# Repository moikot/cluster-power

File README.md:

# Cluster power

Two PCBs designed to provide Raspberry Pis or similar single-board computers with 5V and up to 3A current. 

[Power board](#power-board)  
[Power bridge](#power-bridge)  

## Power board

A circuit diagram and a PCB design for a modular power supply. It's based on a DC-DC step-down voltage buck converter module and can supply a Raspberry Pi or a similar single-board computer with 5V and up to 3A current. 

You can connect several power boards in a chain using [AVX bipolar card edge connector Series 9159](https://no.mouser.com/ProductDetail/581-00915900201106) and provide power to a cluster of Raspberry Pis. 

### Technical characteristics

* Input voltage: 7V-28V DC
* Output voltage: 5V DC
* Output current: 3A. max (2A for a long time)

### Components

* 3 x 7V-28V to 5V DC-DC step-down voltage buck converter [module](https://www.aliexpress.com/item/32728471522.html).
* Fixed Terminal Block [PTSM 0,5/ 2-2,5-H](https://no.mouser.com/ProductDetail/651-1770885).
* 2 postions x 2 rows [board to board connector](https://no.mouser.com/ProductDetail/200-SSW10201GD).
* 100µF 50V Aluminum [electrolytic capacitor](https://www.digikey.no/product-detail/en/panasonic-electronic-components/ECA-1HM101/P5182-ND/245041).

## Power Bridge

A circuit diagram and a PCB design for a small board for connecting  [Power board](#power-board)  to a Raspberry Pi or a similar single-board computer and providing power through its GPIO.

### Components
* 2 postions x 2 rows right angle [header](https://no.mouser.com/ProductDetail/200-TSW10208LDRA).
* 5 postions x 2 rows [board to board connector](https://no.mouser.com/ProductDetail/200-SSW10501GD).

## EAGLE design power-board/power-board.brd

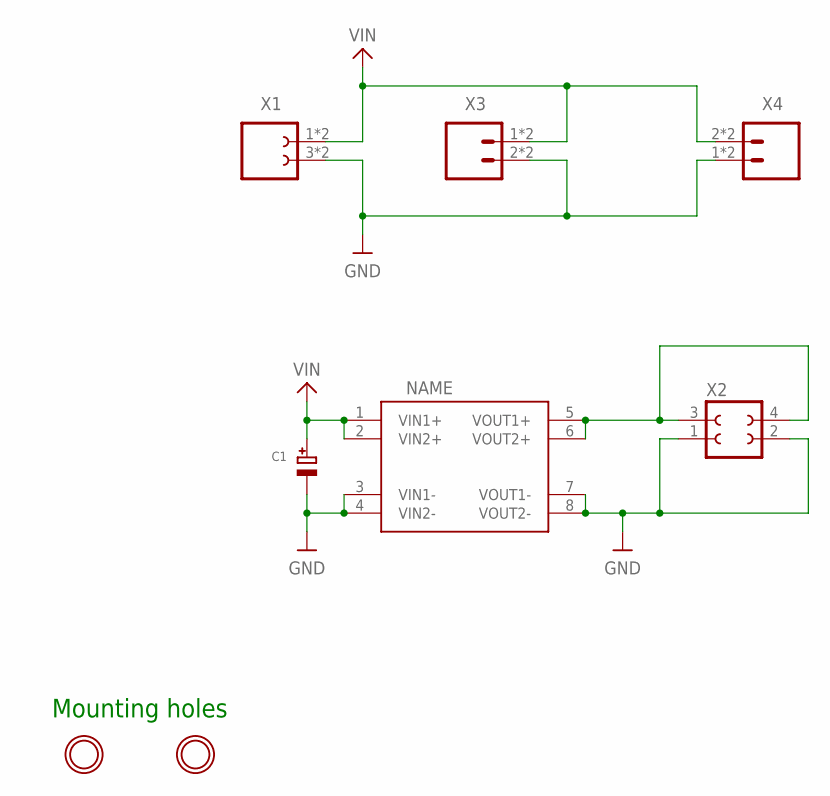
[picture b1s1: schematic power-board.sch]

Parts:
C1: CAP_ELECTROLYTIC; CAPPRD350W60D800H800B
PS1: K8801MODULE; K8801
U$2, U$3: MOUNTINGHOLE2.7_THICK; MOUNTINGHOLE_2.7_PLATED_THICK
X1: CON-FE02-1; PTSM0,5/2-2,5-HTHRR24
X2: CON-FE02-2HDRVR4W64P254_2X2; HDRVR4W64P254_2X2
X3, X4: CON-MA02-1; AVX-BTB-009159002001106

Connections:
GND: C1.2 (-), PS1.3 (VIN1-), PS1.4 (VIN2-), PS1.7 (VOUT1-), PS1.8 (VOUT2-), X1.3, X1.4 (3), X2.1, X2.2, X3.2 (4), X3.4, X4.1 (2), X4.3 (2)
unnamed: PS1.5 (VOUT1+), PS1.6 (VOUT2+), X2.3, X2.4
VIN: C1.1 (+), PS1.1 (VIN1+), PS1.2 (VIN2+), X1.1, X1.2 (1), X3.1 (2), X3.3 (2), X4.2 (4), X4.4

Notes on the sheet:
Mounting holes

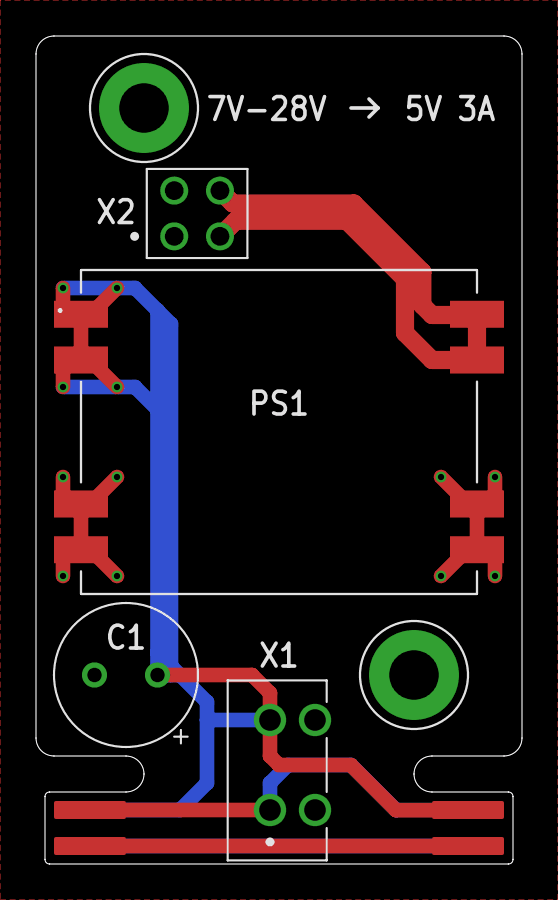
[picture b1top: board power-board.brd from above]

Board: 2 copper layers, 27.0 x 46.0 mm, 8 parts (0 on the bottom side), 3 nets.

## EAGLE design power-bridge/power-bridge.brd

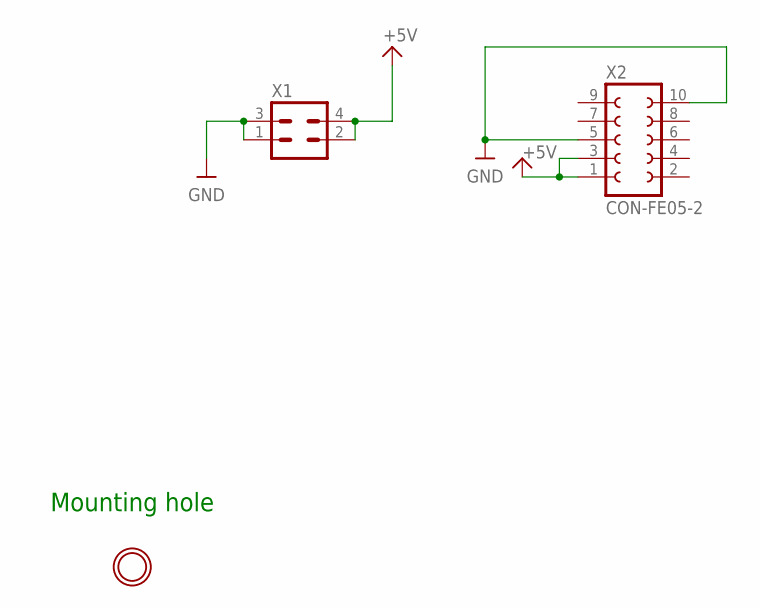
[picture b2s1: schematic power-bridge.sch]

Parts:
U$1: MOUNTINGHOLE2.7_THICK; MOUNTINGHOLE_2.7_PLATED_THICK
X1: CON-MA02-2; HDRRA4W64P254_2X2_508X254X556B
X2: CON-FE05-2; HDRVR10W64P254_2X5_1270X508X850B

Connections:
+5V: X1.2, X1.4, X2.1, X2.3
GND: X1.1, X1.3, X2.5, X2.10

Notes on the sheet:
Mounting hole

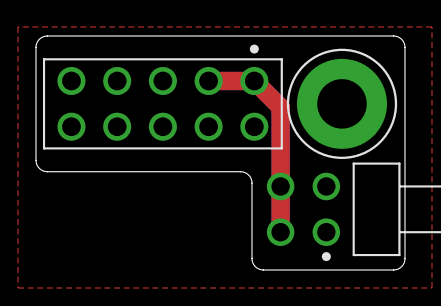
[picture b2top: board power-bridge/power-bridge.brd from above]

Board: 2 copper layers, 20.5 x 13.0 mm, 3 parts (0 on the bottom side), 2 nets.

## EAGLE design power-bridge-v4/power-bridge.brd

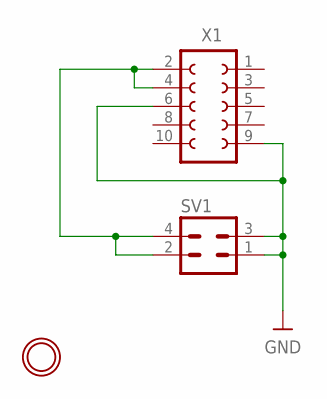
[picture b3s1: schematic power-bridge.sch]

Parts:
SV1: CON-MA02-2; MA02-2W
U$2: MOUNTINGHOLE2.7_THICK; MOUNTINGHOLE_2.7_PLATED_THICK
X1: CON-FE05-2; FE05-2

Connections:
GND: SV1.1, SV1.3, X1.6, X1.9
PWR: SV1.2, SV1.4, X1.2, X1.4

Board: 2 copper layers, 3 parts (0 on the bottom side), 2 nets, no tracks yet.

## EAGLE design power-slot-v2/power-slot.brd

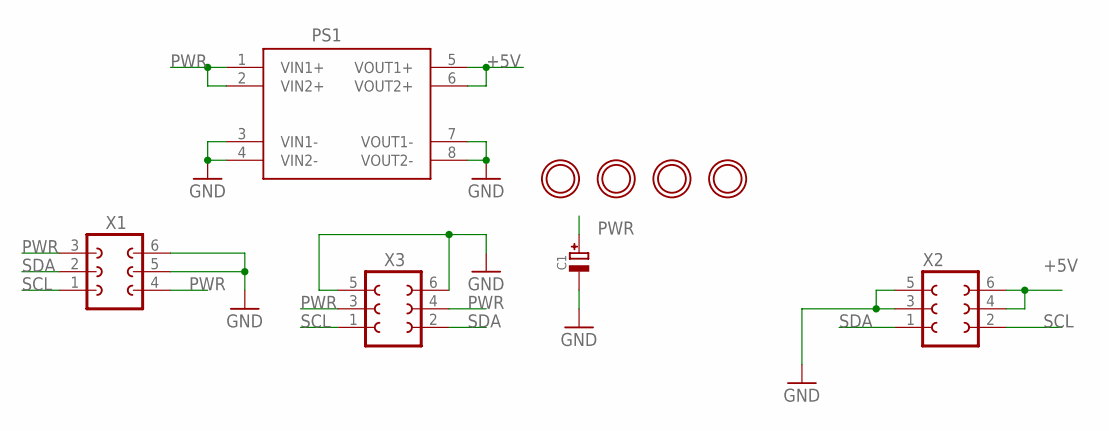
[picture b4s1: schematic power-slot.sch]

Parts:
C1: CAP_ELECTROLYTICPTH_3.5MMGRID_8MMDIA; CELEC_3.5MM_8MM
PS1: K8801MODULE; K8801
U$1, U$2, U$3, U$4: MOUNTINGHOLE2.5_THICK; MOUNTINGHOLE_2.5_PLATED_THICK
X1: CON-MA03-2MA03-2W; MA03-2W
X2: CON-FE03-2CARDEDGE-0.1; FE3-2-CARDEDGE-0.1
X3: FE06-2W

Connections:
+5V: PS1.5 (VOUT1+), PS1.6 (VOUT2+), X2.4, X2.6
GND: C1.-, PS1.3 (VIN1-), PS1.4 (VIN2-), PS1.7 (VOUT1-), PS1.8 (VOUT2-), X1.5, X1.6, X2.3, X2.5, X3.5, X3.6
PWR: C1.+, PS1.1 (VIN1+), PS1.2 (VIN2+), X1.3, X1.4, X3.3, X3.4
SCL: X1.1, X2.2, X3.1
SDA: X1.2, X2.1, X3.2

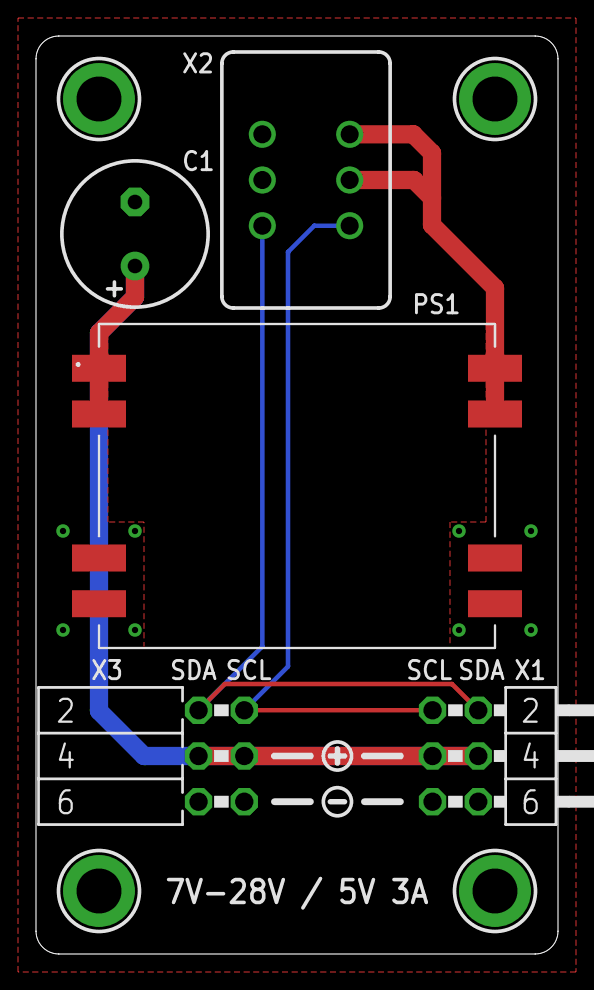
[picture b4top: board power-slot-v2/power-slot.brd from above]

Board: 2 copper layers, 29.0 x 51.0 mm, 11 parts (0 on the bottom side), 5 nets.

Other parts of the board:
U$5: SYMBOL_PLUS
U$6: SYMBOL_MINUS

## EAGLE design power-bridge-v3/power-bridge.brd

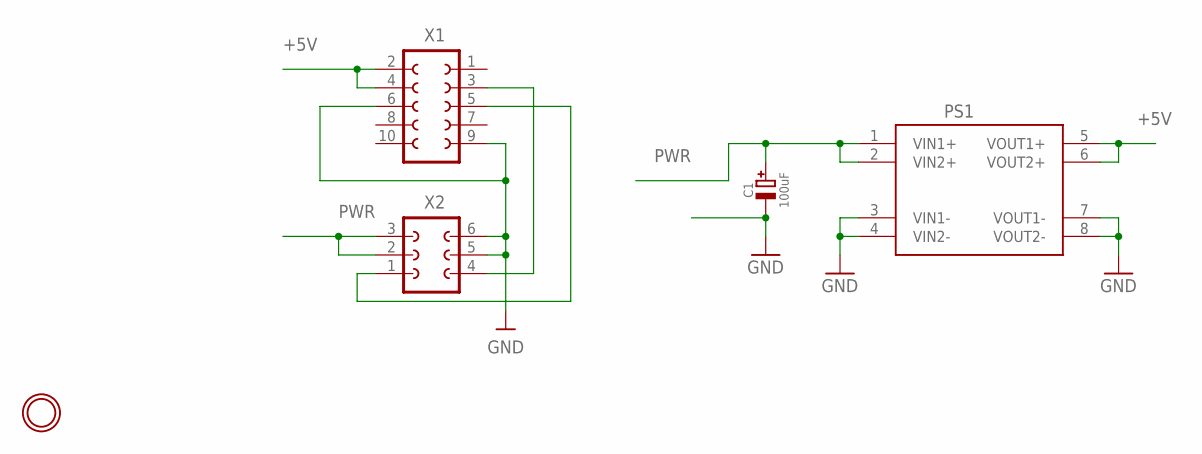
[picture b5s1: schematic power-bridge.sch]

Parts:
C1: 100uF; CELEC_3.5MM_8MM
PS1: K8801MODULE; K8801
U$2: MOUNTINGHOLE2.7_THICK; MOUNTINGHOLE_2.7_PLATED_THICK
X1: CON-FE05-2; FE05-2
X2: CON-MA03-2PCB_EDGE; PCB_EDGE_03-2

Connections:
+5V: PS1.5 (VOUT1+), PS1.6 (VOUT2+), X1.2, X1.4
GND: C1.-, PS1.3 (VIN1-), PS1.4 (VIN2-), PS1.7 (VOUT1-), PS1.8 (VOUT2-), X1.6, X1.9, X2.5, X2.6
unnamed: X1.3, X2.4
unnamed: X1.5, X2.1
PWR: C1.+, PS1.1 (VIN1+), PS1.2 (VIN2+), X2.2, X2.3

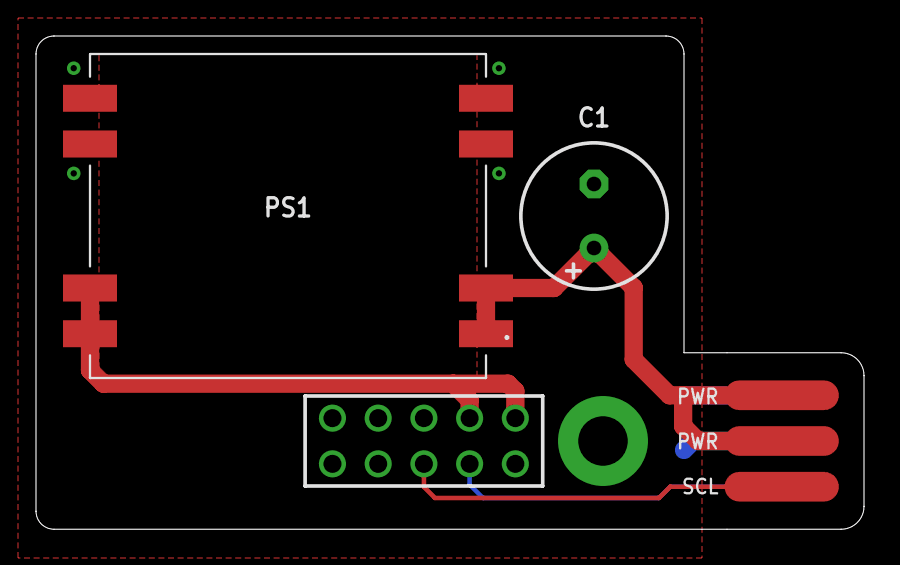
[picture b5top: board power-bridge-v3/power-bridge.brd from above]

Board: 2 copper layers, 46.0 x 27.4 mm, 6 parts (1 on the bottom side), 5 nets.

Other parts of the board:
U$3: CAT_LOGO

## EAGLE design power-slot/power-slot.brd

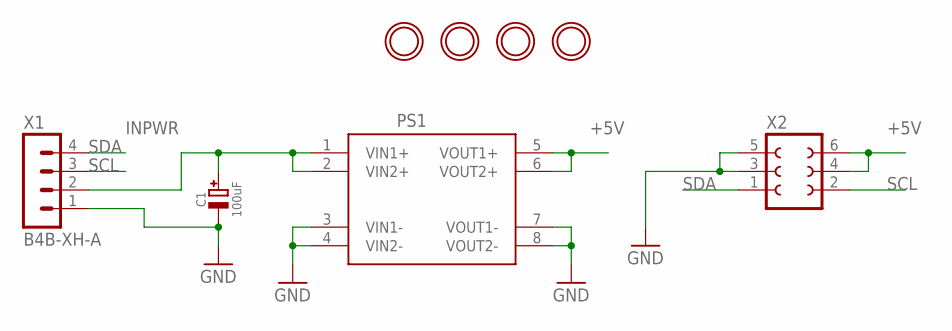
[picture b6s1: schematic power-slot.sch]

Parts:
C1: 100uF; CELEC_3.5MM_8MM
PS1: K8801MODULE; K8801
U$1, U$2, U$3, U$4: MOUNTINGHOLE2.7THIN; MOUNTINGHOLE_2.7_PLATEDTHIN
X1: B4B-XH-A
X2: CON-FE03-2CARDEDGE-0.1; FE3-2-CARDEDGE-0.1

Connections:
+5V: PS1.5 (VOUT1+), PS1.6 (VOUT2+), X2.4, X2.6
GND: C1.-, PS1.3 (VIN1-), PS1.4 (VIN2-), PS1.7 (VOUT1-), PS1.8 (VOUT2-), X1.1, X2.3, X2.5
INPWR: C1.+, PS1.1 (VIN1+), PS1.2 (VIN2+), X1.2
SCL: X1.3, X2.2
SDA: X1.4, X2.1

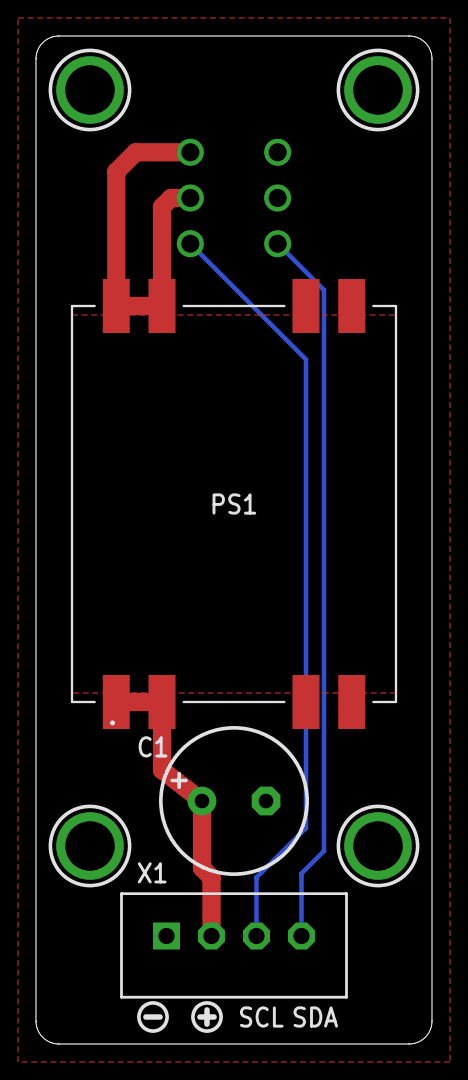
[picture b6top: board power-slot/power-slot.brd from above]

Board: 2 copper layers, 22.0 x 56.0 mm, 10 parts (1 on the bottom side), 5 nets.

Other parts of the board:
U$5: SYMBOL_PLUS
U$6: SYMBOL_MINUS

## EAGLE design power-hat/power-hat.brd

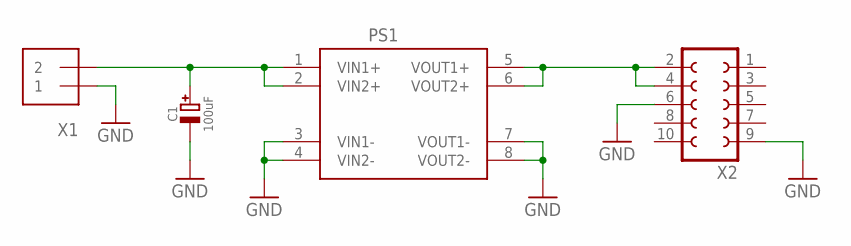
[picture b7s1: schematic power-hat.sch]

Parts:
C1: 100uF; CELEC_3.5MM_8MM
PS1: K8801MODULE; K8801
X1: WR_TBL_1X2-3.5MM; WR-TBL-1X2-3.5MM
X2: FE05-2

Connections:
GND: C1.-, PS1.3 (VIN1-), PS1.4 (VIN2-), PS1.7 (VOUT1-), PS1.8 (VOUT2-), X1.1, X2.6, X2.9
unnamed: C1.+, PS1.1 (VIN1+), PS1.2 (VIN2+), X1.2
PWR: PS1.5 (VOUT1+), PS1.6 (VOUT2+), X2.2, X2.4

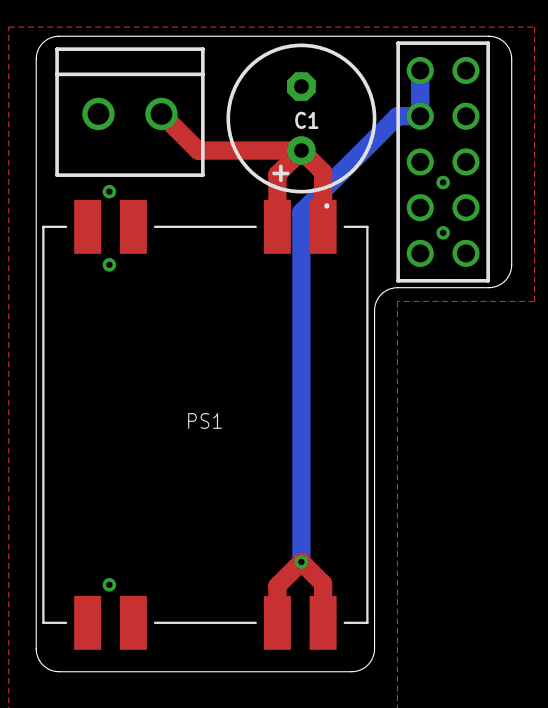
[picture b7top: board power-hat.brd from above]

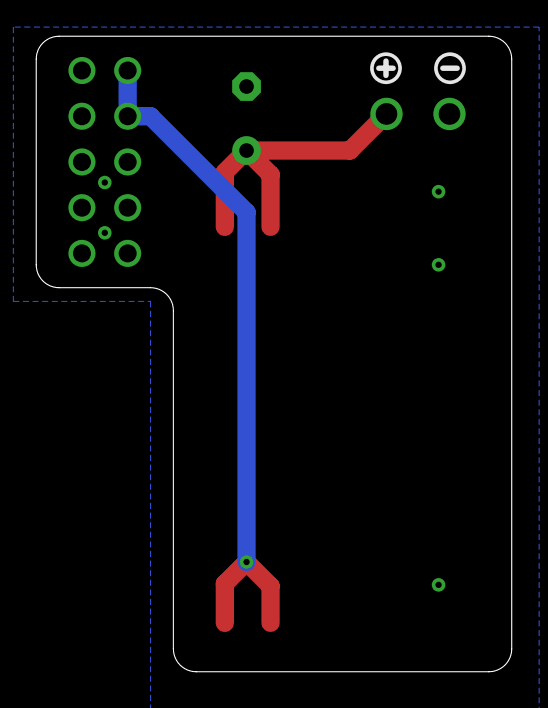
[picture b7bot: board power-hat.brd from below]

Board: 2 copper layers, 26.4 x 35.3 mm, 6 parts (2 on the bottom side), 3 nets.

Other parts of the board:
U$5: SYMBOL_PLUS
U$6: SYMBOL_MINUS

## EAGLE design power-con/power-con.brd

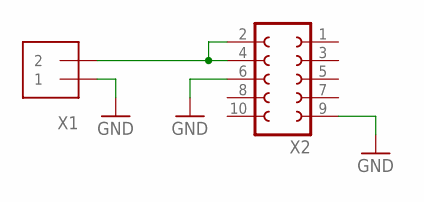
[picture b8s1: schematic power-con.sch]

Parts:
X1: WR_TBL_1X2-3.5MM; WR-TBL-1X2-3.5MM
X2: FE05-2

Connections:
GND: X1.1, X2.6, X2.9
PWR: X1.2, X2.2, X2.4

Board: 2 copper layers, 4 parts (2 on the bottom side), 2 nets, no tracks yet.

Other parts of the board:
U$5: SYMBOL_PLUS
U$6: SYMBOL_MINUS

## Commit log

2019-11-17 Use GitHub URL instead of revision
2019-11-17 Add .gitignore
2019-11-17 Add QR code
2019-11-17 Add a curious cat
2019-11-17 Add smiles
2019-11-17 Create LICENSE
2019-11-17 Improve README
2019-12-04 Add power connector
2020-01-09 Add Power-Hat
2020-01-11 Add power bridge
2020-01-11 Add power slot
2020-01-12 Finalize Power slot
2020-01-12 Board outline fix
2020-02-04 Add power bridge v3
2020-02-08 Add a new version of Power Slot
2020-08-23 Add v4 bridge and v3 powers slot
2020-10-09 Publish v1.0.0 Power Board and Power Bridge

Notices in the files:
parts and their libraries:
microbuilder: This work is placed in the public domain, and may be freely used for commercial and non-commercial work with the following conditions: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
